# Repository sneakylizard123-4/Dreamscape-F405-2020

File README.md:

# Dreamscape F405

a 20x20mm flight controller for 3" fpv drone

## Why I made this

would be a nice portfolio project
if it works i save lots of money too

## Pictures

| Page | Sheet |
|---|---|
| 1 | [Root / block diagram](images/schematic/Dreamscape-F405-2020.png) |
| 2 | [Power](images/schematic/Dreamscape-F405-2020-Power.png) |
| 3 | [Sensors](images/schematic/Dreamscape-F405-2020-Sensors.png) |
| 4 | [Blackbox](images/schematic/Dreamscape-F405-2020-Blackbox.png) |
| 5 | [OSD](images/schematic/Dreamscape-F405-2020-OSD.png) |
| 6 | [STM32](images/schematic/Dreamscape-F405-2020-STM32.png) |
| 7 | [Pads / connectors](images/schematic/Dreamscape-F405-2020-Pads.png) |
| 8 | [USB](images/schematic/Dreamscape-F405-2020-USB.png) |

## Features

- **MCU**: STM32F405VGT6
- **IMU**: ICM-42688-P
- **Barometer**: BMP280
- **OSD**: AT7456E (MAX7456-compatible)
- **Blackbox**: full-size microSD slot
- **Receiver**: dedicated JST-SH 4-pin ExpressLRS connector
- **UARTs**: 4 exposed plus I2C pads
- **Power**:
  - Battery input up to 6S
  - 5 V rail: onboard buck regulator
  - 3.3 V rail: TLV75733 LDO
  - 10 V rail: separate buck to feed camera/VTX
  - Onboard battery voltage ADC divider and ESC current sensor input
- **Extras**: beeper driver, neopixel LED strip driver, status LEDs

## Power tree

```mermaid
graph LR
    BAT[Battery +BATT] --> BUCK10[LMR51430 buck]
    BAT --> BUCK5[LMR51430 buck]
    BUCK10 -->|10 V, switched by 10V_EN| R10[CAM / VTX]
    BUCK5 -->|+5V_BUCK| MUX[TPS2116 power mux]
    USB[USB +5V] --> MUX
    MUX -->|system +5V| PERIPH[OSD / ELRS / peripherals]
    PERIPH --> LDO[TLV75733 LDO]
    LDO -->|+3.3V| MCU[STM32F405 / sensors]
```

## Pinout

Solder pads along the edge:

| Pad | Function | Pad | Function |
|---|---|---|---|
| `BAT` | Battery positive | `G` | Ground |
| `3v3` | 3.3 V out | `5v` | 5 V out |
| `10v` | 10 V out (switchable) | `CUR` | ESC current sense in |
| `TEL` | ESC telemetry | `CC` | Camera control |
| `CAM` | Video in from camera | `VTX` | Video out to VTX |
| `M1`-`M4` | Motor PWM outputs | `LED` | Addressable LED strip |
| `BZ+`/`BZ-` | Beeper | `SDA`/`SCL` | I2C |
| `T1`/`R1` | UART1 TX/RX | `T2`/`R2` | UART2 TX/RX |
| `T3`/`R3` | UART3 TX/RX | `T6`/`R6` | UART6 TX/RX |

Connectors:

| Connector | Pins | Use |
|---|---|---|
| J41 - JST-SH 8-pin vertical | BAT, GND, CUR, TEL, M1-M4 | battery + ESC harness |
| J42 - JST-SH 4-pin horizontal | 5V, GND, TX, RX | ExpressLRS receiver |

## Assembly

you probably should get pcba

solder front side first.
hand solder back side

## Flashing

drag the `.bin` onto the mounted DFU drive using the Betaflight Configurator firmware flasher.

Notes:
- If DFU is not accessible, flash via SWD with an ST-Link and `STM32_Programmer_CLI` or OpenOCD instead.

## Known Issues

- Board hasn't been manufactured yet.

## Credits

- OpenDrone
- Betaflight project - firmware this board will run
- STMicroelectronics / TDK / Bosch / Analog Devices datasheets for part reference designs

---

## BOM

| Refs | Part | Package / Footprint | Notes |
|---|---|---|---|
| U1 | STM32F405VGT6 | LQFP-100 14x14 mm | main MCU, 168 MHz Cortex-M4 |
| U6 | ICM-42688-P | LGA-14 | gyro + accel |
| U7 | BMP280 | LGA-8 | barometer |
| U8 | AT7456E | TQFP | MAX7456-compatible OSD |
| Y1 | 27 MHz crystal | 2016 4-pad | OSD clock |
| Card1 | TF-021B-H265 | microSD push-pull slot | blackbox logging |
| U3, U4 | LMR51430 | SOT-23-6 | 3 A buck regulators (10 V and 5 V) |
| U5 | TPS2116DRLR | SOT-583-8 | USB/buck power mux |
| U2 | TLV75733PDBV | SOT-23-5 | 3.3 V LDO |
| Q5, Q6 | AP1606 | DFN-3 | beeper and LED strip drivers |
| D3, D6 | RB161QS-40 | SOD-882 | Schottky diodes (power path) |
| L2, L3 | XRTC303020D4R7 | 3x3 mm | 4.7 uH power inductors |
| D2 | Blue LED | 0402 | status |
| D4, D5, D7 | Green LED | 0402 | power indicators |
| J41 | JST-SH 8-pin | SM08B-SHLS-TF | battery/ESC harness |
| J42 | JST-SH 4-pin | SM04B-SRSS-TB | ELRS receiver |
| R31, R29, R27, R23, R50 | 100 kOhm x5 | 0201 | |
| R2, R39, R49, R50 | 10 kOhm x4 | 0201 | VBAT divider / pull-ups |
| R28 | 39 kOhm | 0201 | buck feedback divider |
| R34, R33 | 7.5 kOhm x2 | 0201 | buck feedback dividers |
| R32 | 13.7 kOhm | 0201 | buck feedback |
| R30 | 6.49 kOhm | 0201 | buck feedback |
| R53, R52 | 75 Ohm x2 | 0201 | |
| R36 | 510 Ohm | 0201 | |
| R51 | 2.4 kOhm | 0201 | |
| R9 | 1 kOhm | 0201 | current sensor filter |
| C24, C25 | 4.7 uF 50 V x2 | 0805 | battery input |
| C29, C28, C34 | 22 uF x3 | 0603/0402 | buck outputs |
| C30 | 4.7 uF | 0402 | |
| C1, C22 | 2.2 uF x2 | 0402 | |
| C4, C36-C39, C43, C32, C26, C27 | 100 nF x10 | 0201 | decoupling |

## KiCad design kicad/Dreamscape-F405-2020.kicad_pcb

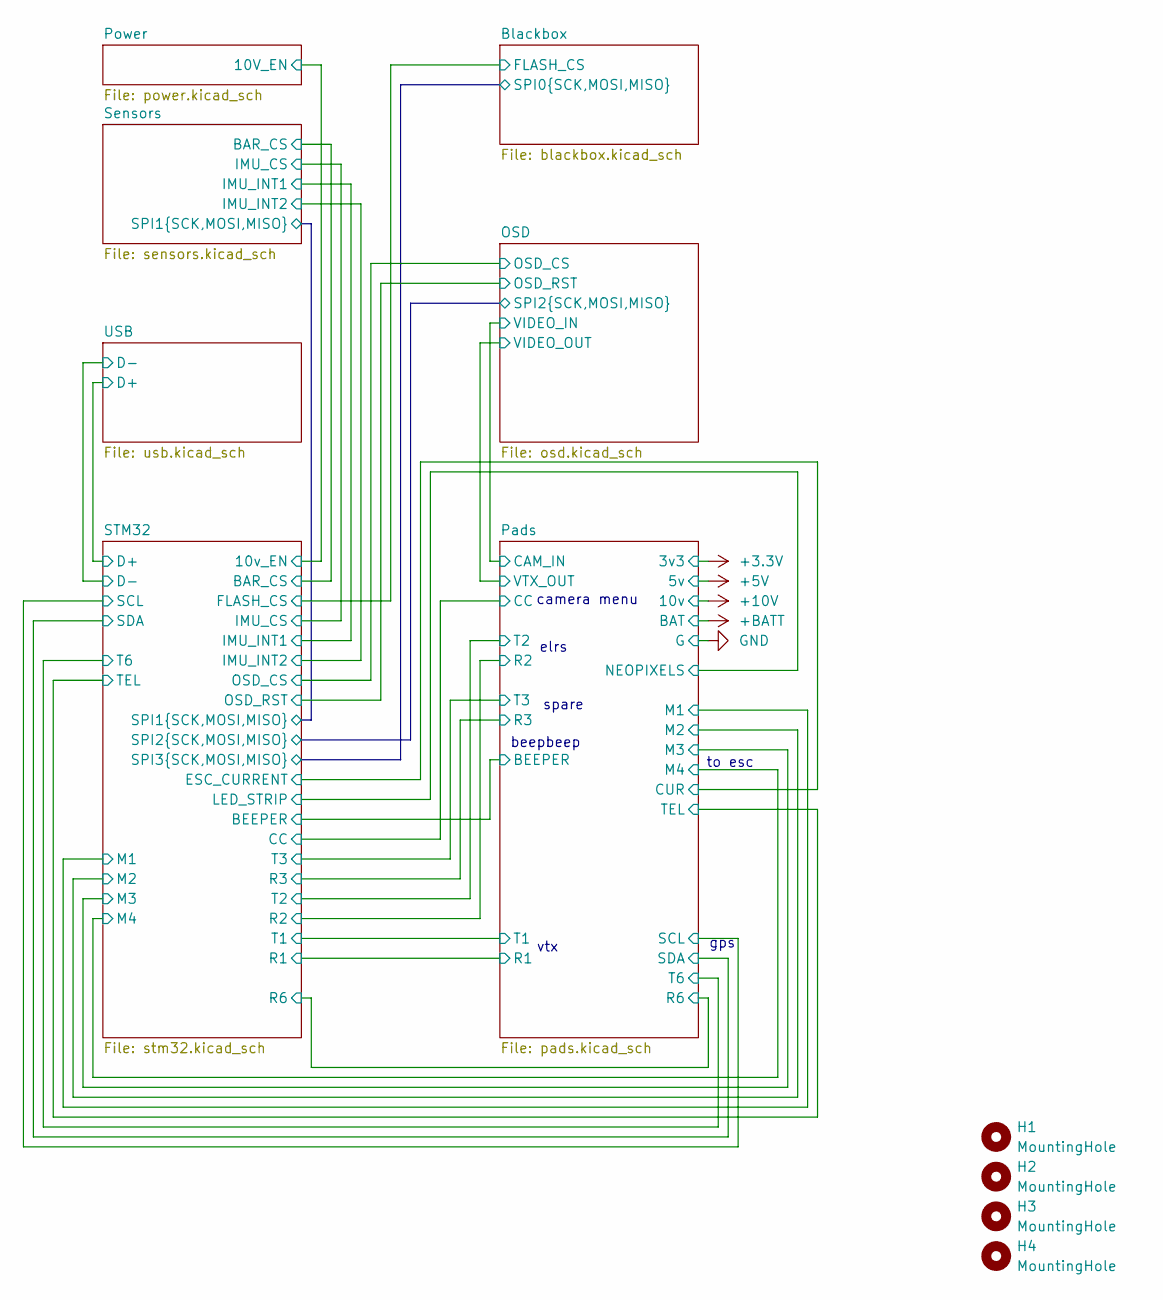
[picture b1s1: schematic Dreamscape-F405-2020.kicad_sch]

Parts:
H1, H2, H3, H4: MountingHole; MountingHole_3.2mm_M3

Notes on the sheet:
beepbeep
gps
spare
camera menu
elrs
to esc
vtx

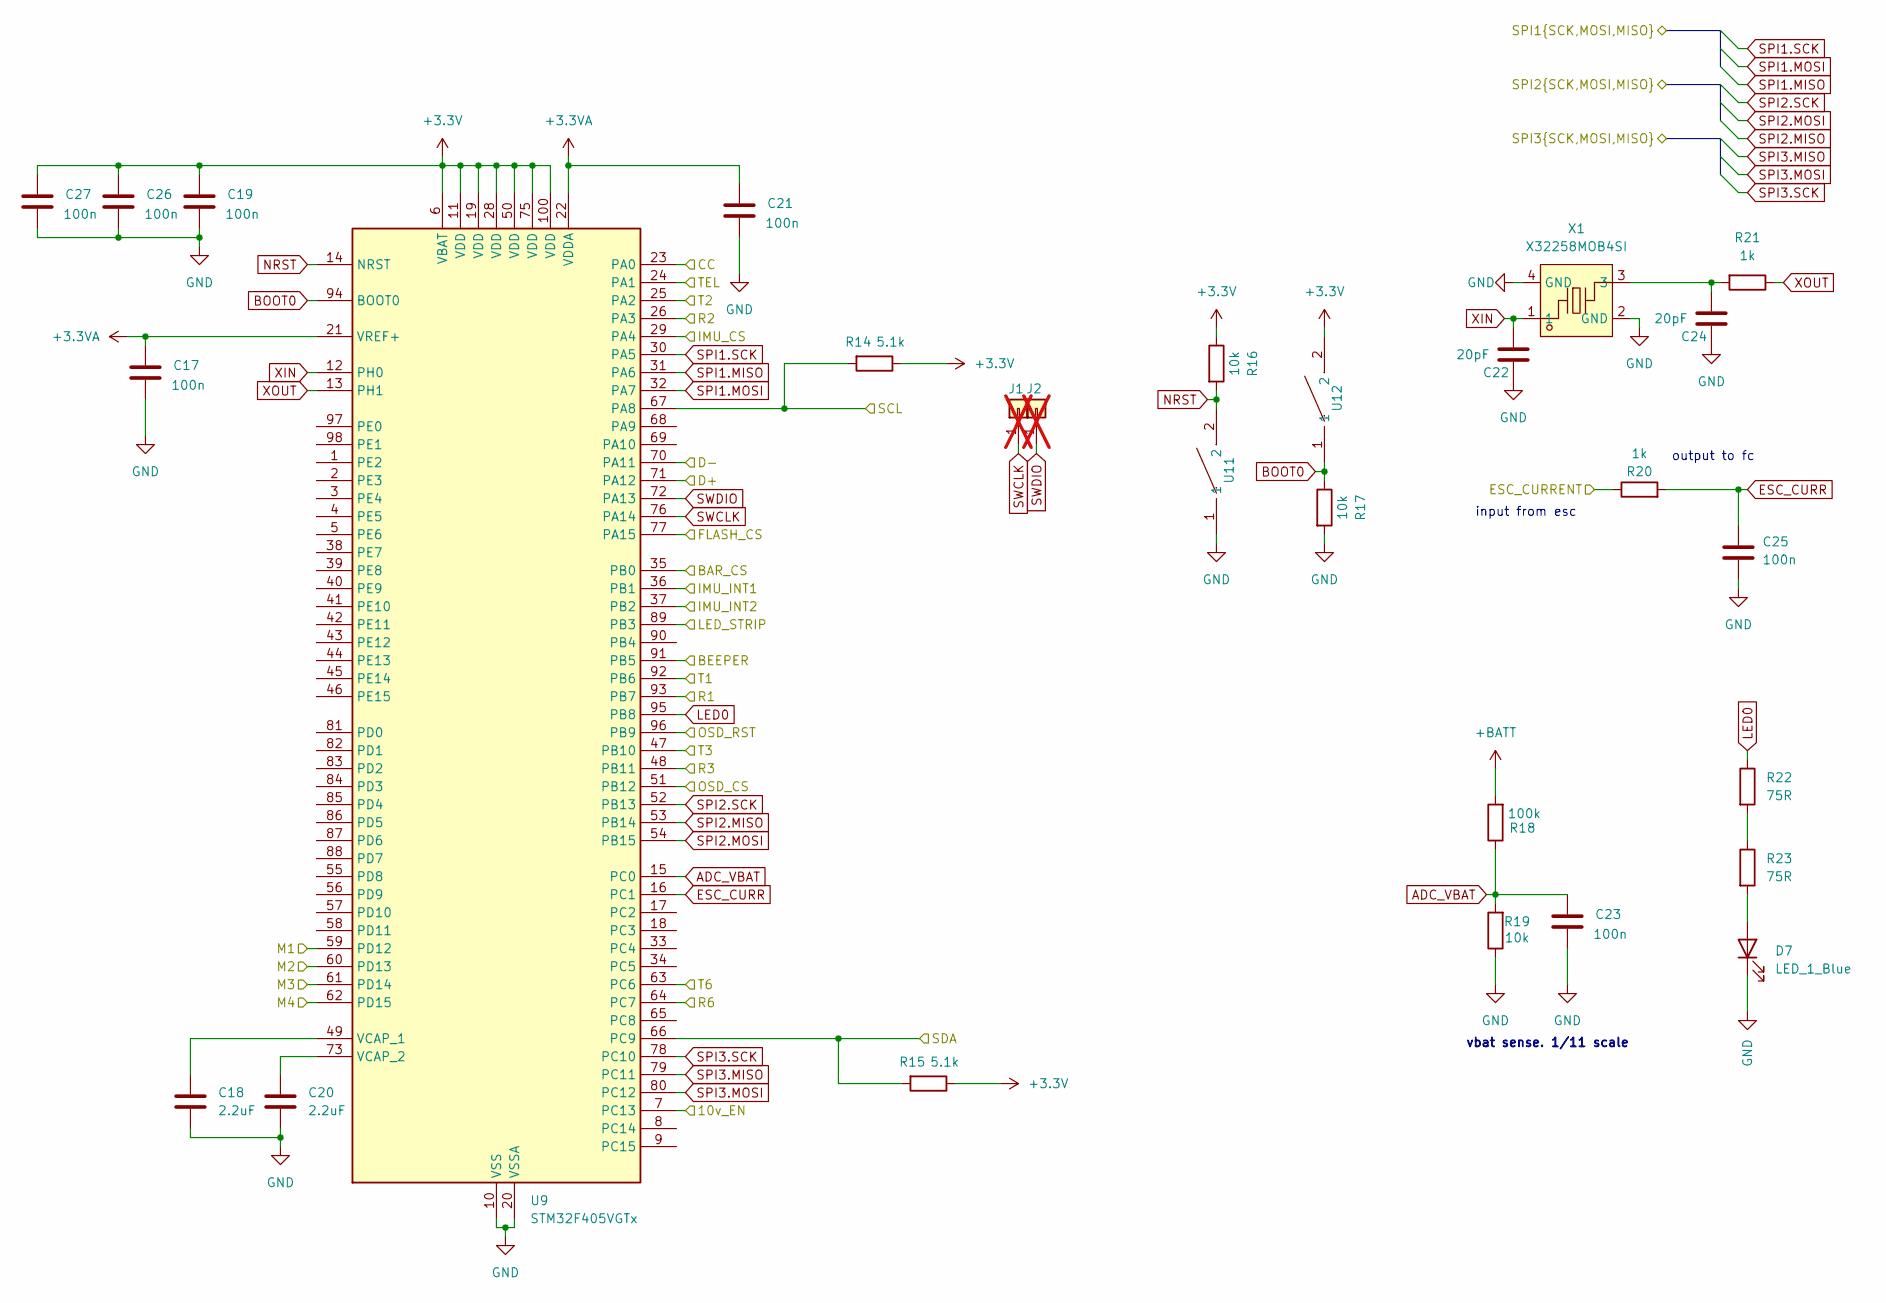
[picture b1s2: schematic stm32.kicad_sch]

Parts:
C17, C19, C21, C23, C25, C26, C27: 100n; C_0201_0603Metric; MPN GRM033R61E104KE14D; LCSC C76939
C18, C20: 2.2uF; C_0402_1005Metric
C22, C24: 20pF; C_0201_0603Metric; MPN GRM0335C1H200JA01D; LCSC C76923
D7: LED_1_Blue; LED_0402_1005Metric; MPN XL-1005UBC; LCSC C22355736
J1, J2: 5V; small_pad; not fitted
R14, R15: 5.1k; R_0201_0603Metric; MPN 0201WMF5101TEE; LCSC C270344
R16, R17, R19: 10k; R_0201_0603Metric; MPN RC0201FR-0710KL; LCSC C106225
R18: 100k; R_0201_0603Metric; MPN 0201WMF1003TEE; LCSC C270364
R20, R21: 1k; R_0201_0603Metric; MPN 0201WMF1001TEE; LCSC C270365
R22, R23: 75R; R_0201_0603Metric; MPN RC0201FR-0775RL; LCSC C274878
U9: STM32F405VGTx; LQFP-100_14x14mm_P0.5mm
U11, U12: TS2306A 240GF MSM 9_C2976675; SW-SMD_4P-L3.0-W2.0-P0.85-LS3.5; MPN TS2306A 240gf MSM 9; LCSC C2976675
X1: X32258MOB4SI; CRYSTAL-SMD_4P-L2.5-W2.0-BL-A; MPN X32258MOB4SI; LCSC C2682775

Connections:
+3.3V: C19.2, C26.2, C27.2, R14.1, R15.1, R16.1, U9.6 (VBAT), U9.11 (VDD), U9.19 (VDD), U9.28 (VDD), U9.50 (VDD), U9.75 (VDD), U9.100 (VDD), U12.2; also elsewhere on the board
+3.3VA: C17.2, C21.2, U9.21 (VREF+), U9.22 (VDDA); also elsewhere on the board
+BATT: R18.2; also elsewhere on the board
/Blackbox/FLASH_CS: U9.77 (PA15); also elsewhere on the board
/OSD/OSD_CS: U9.51 (PB12); also elsewhere on the board
/OSD/OSD_RST: U9.96 (PB9); also elsewhere on the board
/Pads/BEEPER: U9.91 (PB5); also elsewhere on the board
/Pads/CC: U9.23 (PA0); also elsewhere on the board
/Pads/CUR: R20.1; also elsewhere on the board
/Pads/M1: U9.59 (PD12); also elsewhere on the board
/Pads/M2: U9.60 (PD13); also elsewhere on the board
/Pads/M3: U9.61 (PD14); also elsewhere on the board
/Pads/M4: U9.62 (PD15); also elsewhere on the board
/Pads/NEOPIXELS: U9.89 (PB3); also elsewhere on the board
/Pads/R1: U9.93 (PB7); also elsewhere on the board
/Pads/R2: U9.26 (PA3); also elsewhere on the board
/Pads/R3: U9.48 (PB11); also elsewhere on the board
/Pads/R6: U9.64 (PC7); also elsewhere on the board
/Pads/SCL: R15.2, U9.66 (PC9); also elsewhere on the board
/Pads/SDA: R14.2, U9.67 (PA8); also elsewhere on the board
/Pads/T1: U9.92 (PB6); also elsewhere on the board
/Pads/T2: U9.25 (PA2); also elsewhere on the board
/Pads/T3: U9.47 (PB10); also elsewhere on the board
/Pads/T6: U9.63 (PC6); also elsewhere on the board
/Pads/TEL: U9.24 (PA1); also elsewhere on the board
/Power/10V_EN: U9.7 (PC13); also elsewhere on the board
/STM32/BAR_CS: U9.35 (PB0); also elsewhere on the board
/STM32/D+: U9.71 (PA12); also elsewhere on the board
/STM32/D-: U9.70 (PA11); also elsewhere on the board
/STM32/IMU_CS: U9.29 (PA4); also elsewhere on the board
/STM32/IMU_INT1: U9.36 (PB1); also elsewhere on the board
/STM32/IMU_INT2: U9.37 (PB2); also elsewhere on the board
ADC_VBAT: C23.2, R18.1, R19.2, U9.15 (PC0)
BOOT0: R17.1, U9.94 (BOOT0), U12.1
ESC_CURR: C25.1, R20.2, U9.16 (PC1)
GND: C17.1, C18.2, C19.1, C20.2, C21.1, C22.1, C23.1, C24.1, C25.2, C26.1, C27.1, D7.1 (K), R17.2, R19.1, U9.10 (VSS), U9.20 (VSSA), U9.27 (VSS), U9.74 (VSS), U9.99 (VSS), U11.1, X1.2 (GND), X1.4 (GND); also elsewhere on the board
LED0: R22.1, U9.95 (PB8)
NRST: R16.2, U9.14 (NRST), U11.2
unnamed: C24.2, R21.2, X1.3
unnamed: D7.2 (A), R23.2
unnamed: R22.2, R23.1
unnamed: C18.1, U9.49 (VCAP_1)
unnamed: C20.1, U9.73 (VCAP_2)
SPI1.MISO: U9.31 (PA6); also elsewhere on the board
SPI1.MOSI: U9.32 (PA7); also elsewhere on the board
SPI1.SCK: U9.30 (PA5); also elsewhere on the board
SPI2.MISO: U9.53 (PB14); also elsewhere on the board
SPI2.MOSI: U9.54 (PB15); also elsewhere on the board
SPI2.SCK: U9.52 (PB13); also elsewhere on the board
SPI3.MISO: U9.79 (PC11); also elsewhere on the board
SPI3.MOSI: U9.80 (PC12); also elsewhere on the board
SPI3.SCK: U9.78 (PC10); also elsewhere on the board
SWCLK: J1.1 (Pin_1_1), U9.76 (PA14)
SWDIO: J2.1 (Pin_1_1), U9.72 (PA13)
XIN: C22.2, U9.12 (PH0), X1.1
XOUT: R21.1, U9.13 (PH1)

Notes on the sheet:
input from esc
vbat sense. 1/11 scale
output to fc

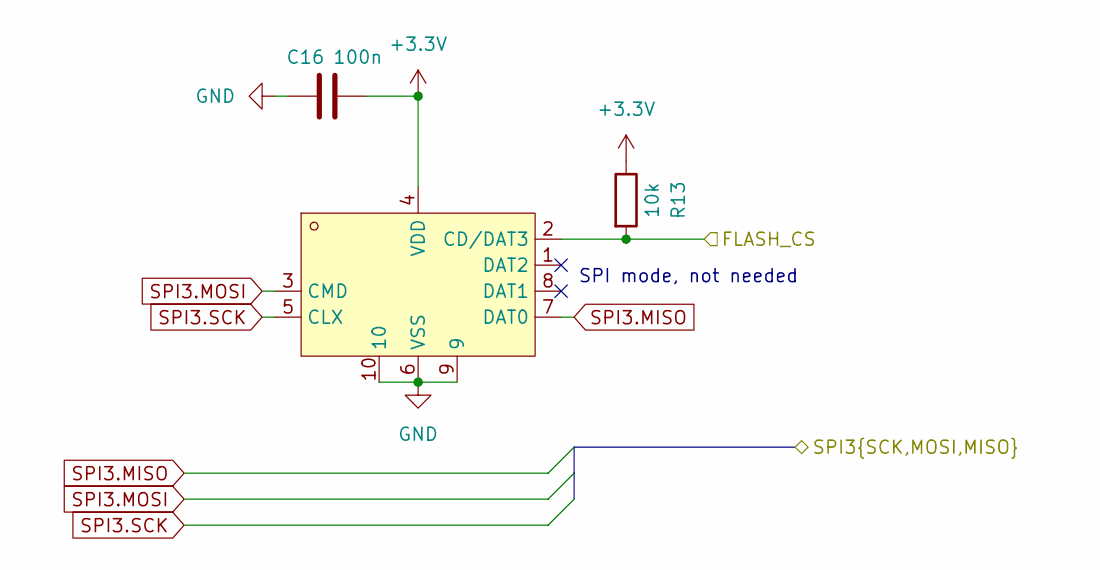
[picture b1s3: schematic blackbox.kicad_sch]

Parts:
C16: 100n; C_0201_0603Metric; MPN GRM033R61E104KE14D; LCSC C76939
Card1: TF-021B-H265; TF-SMD_TF-021B-H265; LCSC C498185
R13: 10k; R_0201_0603Metric; MPN RC0201FR-0710KL; LCSC C106225

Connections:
+3.3V: C16.1, Card1.4 (VDD), R13.1; also elsewhere on the board
/Blackbox/FLASH_CS: Card1.2 (CD/DAT3), R13.2; also elsewhere on the board
GND: C16.2, Card1.6 (VSS), Card1.9, Card1.10; also elsewhere on the board
SPI3.MISO: Card1.7 (DAT0); also elsewhere on the board
SPI3.MOSI: Card1.3 (CMD); also elsewhere on the board
SPI3.SCK: Card1.5 (CLX); also elsewhere on the board

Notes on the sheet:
SPI mode, not needed

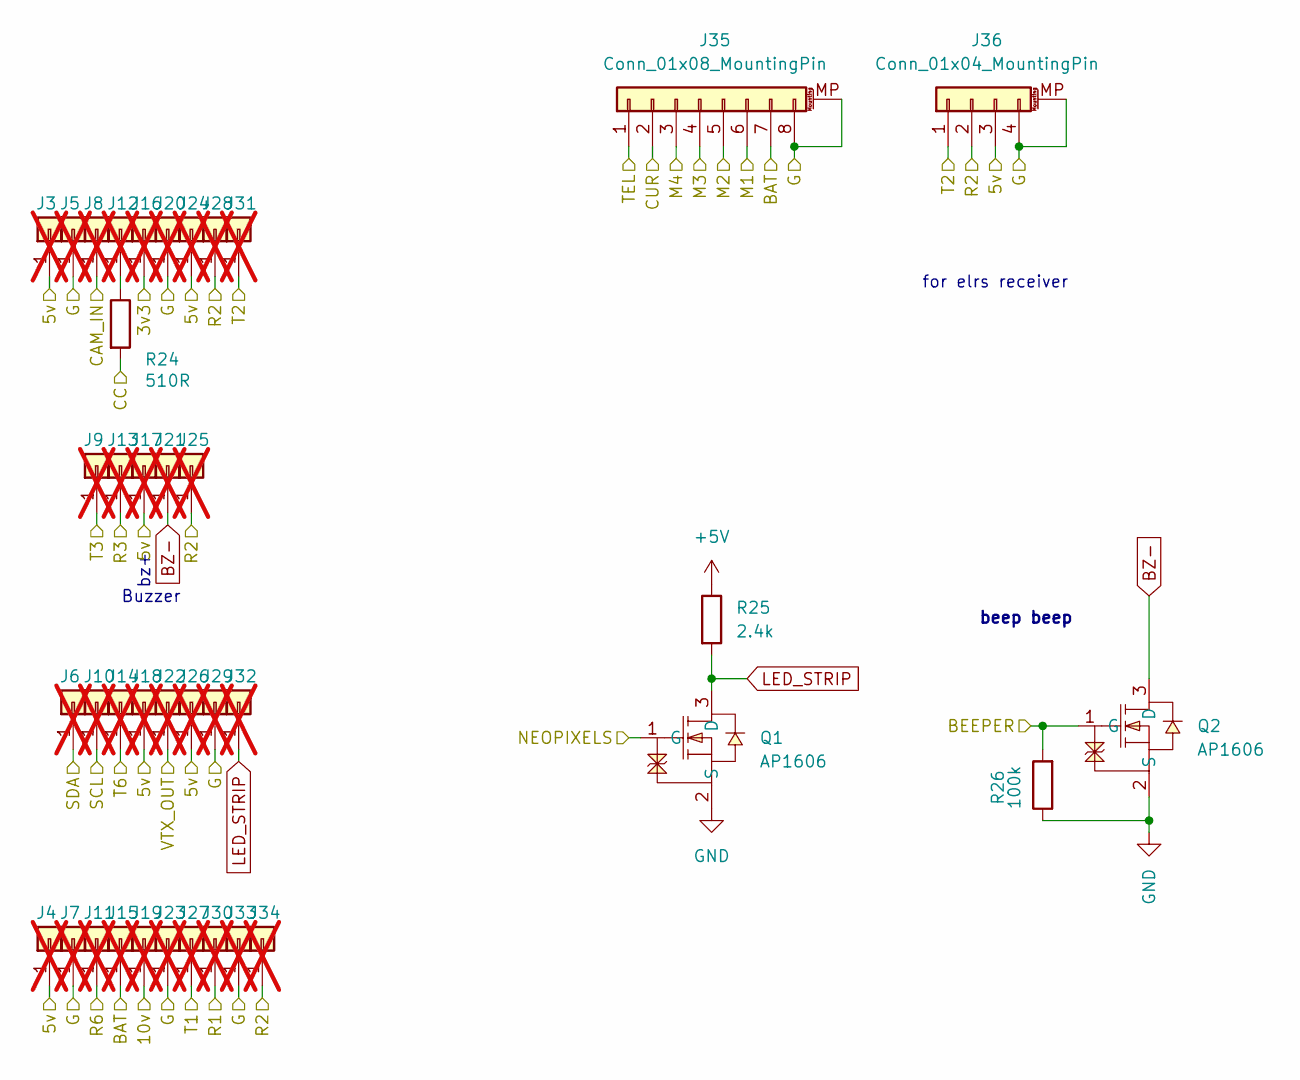
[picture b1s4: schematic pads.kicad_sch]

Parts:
J3, J4, J5, J6, J7, J8, J9, J10, J11, J12, J13, J14, J15, J16, J17, J18, J19, J20, J21, J22, J23, J24, J25, J26, J27, J28, J29, J30, J31, J32, J33, J34: 5V; small_pad; not fitted
J35: Conn_01x08_MountingPin; JST_SHL_SM08B-SHLS-TF_1x08-1MP_P1.00mm_Horizontal
J36: Conn_01x04_MountingPin; JST_SH_SM04B-SRSS-TB_1x04-1MP_P1.00mm_Horizontal
Q1, Q2: AP1606; DFN-3L_L1.0-W0.6-P0.65-BR; MPN AP1606; LCSC C2849580
R24: 510R; R_0201_0603Metric; LCSC C57784
R25: 2.4k; R_0201_0603Metric; LCSC C166281
R26: 100k; R_0201_0603Metric; MPN 0201WMF1003TEE; LCSC C270364

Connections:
+3.3V: J16.1 (Pin_1_1); also elsewhere on the board
+5V: J3.1 (Pin_1_1), J4.1 (Pin_1_1), J17.1 (Pin_1_1), J18.1 (Pin_1_1), J24.1 (Pin_1_1), J26.1 (Pin_1_1), J36.3, R25.1; also elsewhere on the board
+10V: J19.1 (Pin_1_1); also elsewhere on the board
+BATT: J15.1 (Pin_1_1), J35.7; also elsewhere on the board
/OSD/VIDEO_IN: J8.1 (Pin_1_1); also elsewhere on the board
/OSD/VIDEO_OUT: J22.1 (Pin_1_1); also elsewhere on the board
/Pads/BEEPER: Q2.1 (G), R26.2; also elsewhere on the board
/Pads/CC: R24.2; also elsewhere on the board
/Pads/CUR: J35.2; also elsewhere on the board
/Pads/M1: J35.6; also elsewhere on the board
/Pads/M2: J35.5; also elsewhere on the board
/Pads/M3: J35.4; also elsewhere on the board
/Pads/M4: J35.3; also elsewhere on the board
/Pads/NEOPIXELS: Q1.1 (G); also elsewhere on the board
/Pads/R1: J30.1 (Pin_1_1); also elsewhere on the board
/Pads/R2: J25.1 (Pin_1_1), J28.1 (Pin_1_1), J34.1 (Pin_1_1), J36.2; also elsewhere on the board
/Pads/R3: J13.1 (Pin_1_1); also elsewhere on the board
/Pads/R6: J11.1 (Pin_1_1); also elsewhere on the board
/Pads/SCL: J10.1 (Pin_1_1); also elsewhere on the board
/Pads/SDA: J6.1 (Pin_1_1); also elsewhere on the board
/Pads/T1: J27.1 (Pin_1_1); also elsewhere on the board
/Pads/T2: J31.1 (Pin_1_1), J36.1; also elsewhere on the board
/Pads/T3: J9.1 (Pin_1_1); also elsewhere on the board
/Pads/T6: J14.1 (Pin_1_1); also elsewhere on the board
/Pads/TEL: J35.1; also elsewhere on the board
BZ-: J21.1 (Pin_1_1), Q2.3 (D)
GND: J5.1 (Pin_1_1), J7.1 (Pin_1_1), J20.1 (Pin_1_1), J23.1 (Pin_1_1), J29.1 (Pin_1_1), J33.1 (Pin_1_1), J35.8, J35.MP (MountPin), J36.4, J36.MP (MountPin), Q1.2 (S), Q2.2 (S), R26.1; also elsewhere on the board
LED_STRIP: J32.1 (Pin_1_1), Q1.3 (D), R25.2
unnamed: J12.1 (Pin_1_1), R24.1

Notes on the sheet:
Buzzer
beep beep
bz+
for elrs receiver

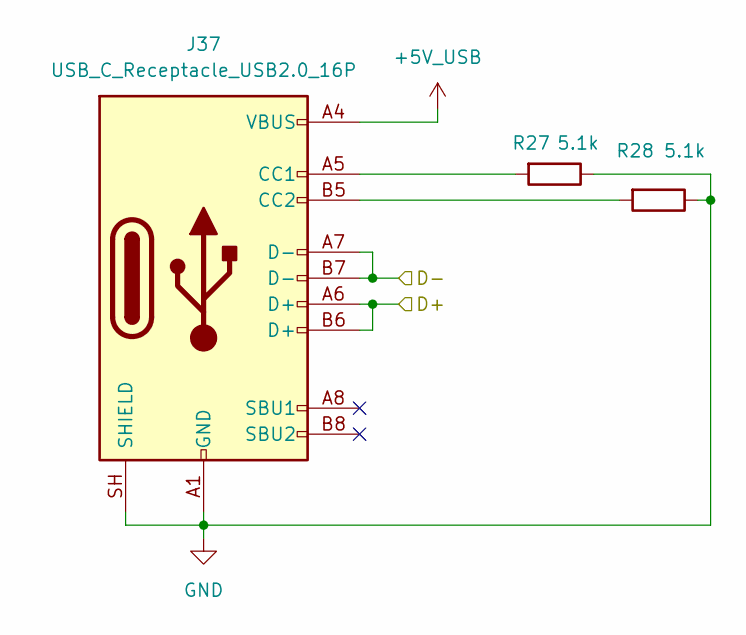
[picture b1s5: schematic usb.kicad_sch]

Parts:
J37: USB_C_Receptacle_USB2.0_16P; USB_C_Receptacle_HRO_TYPE-C-31-M-12
R27, R28: 5.1k; R_0201_0603Metric; MPN 0201WMF5101TEE; LCSC C270344

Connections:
+5V_USB: J37.A4 (VBUS), J37.A9 (VBUS), J37.B4 (VBUS), J37.B9 (VBUS); also elsewhere on the board
/STM32/D+: J37.A6 (D+), J37.B6 (D+); also elsewhere on the board
/STM32/D-: J37.A7 (D-), J37.B7 (D-); also elsewhere on the board
GND: J37.A1 (GND), J37.A12 (GND), J37.B1 (GND), J37.B12 (GND), J37.SH (SHIELD), R27.1, R28.1; also elsewhere on the board
unnamed: J37.A5 (CC1), R27.2
unnamed: J37.B5 (CC2), R28.2

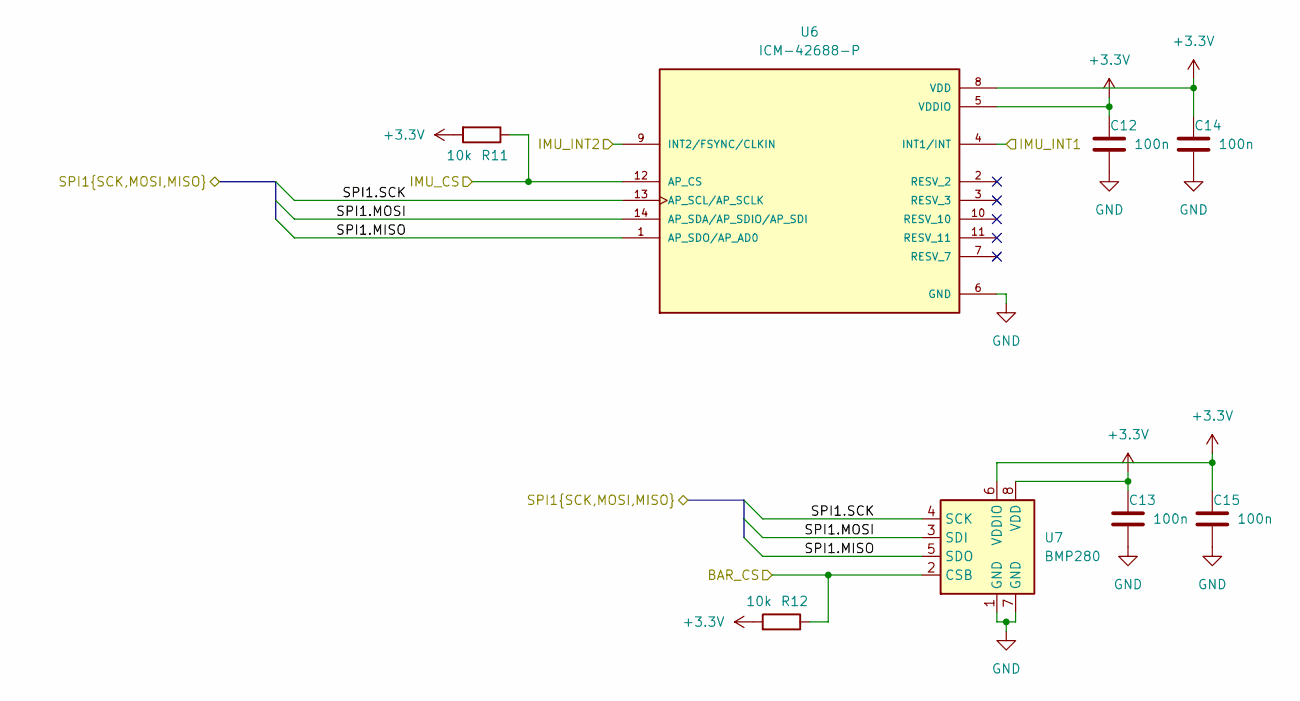
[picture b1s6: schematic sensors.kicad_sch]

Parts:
C12, C13, C14, C15: 100n; C_0201_0603Metric; MPN GRM033R61E104KE14D; LCSC C76939
R11, R12: 10k; R_0201_0603Metric; MPN RC0201FR-0710KL; LCSC C106225
U6: ICM-42688-P; PQFN50P300X250X97-14N; PARTREV 1.2
U7: BMP280; Bosch_LGA-8_2x2.5mm_P0.65mm_ClockwisePinNumbering

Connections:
+3.3V: C12.1, C13.1, C14.1, C15.1, R11.2, R12.2, U6.5 (VDDIO), U6.8 (VDD), U7.6 (VDDIO), U7.8 (VDD); also elsewhere on the board
/STM32/BAR_CS: R12.1, U7.2 (CSB); also elsewhere on the board
/STM32/IMU_CS: R11.1, U6.12 (AP_CS); also elsewhere on the board
/STM32/IMU_INT1: U6.4 (INT1/INT); also elsewhere on the board
/STM32/IMU_INT2: U6.9 (INT2/FSYNC/CLKIN); also elsewhere on the board
GND: C12.2, C13.2, C14.2, C15.2, U6.6 (GND), U7.1 (GND), U7.7 (GND); also elsewhere on the board
SPI1.MISO: U6.1 (AP_SDO/AP_AD0), U7.5 (SDO); also elsewhere on the board
SPI1.MOSI: U6.14 (AP_SDA/AP_SDIO/AP_SDI), U7.3 (SDI); also elsewhere on the board
SPI1.SCK: U6.13 (AP_SCL/AP_SCLK), U7.4 (SCK); also elsewhere on the board

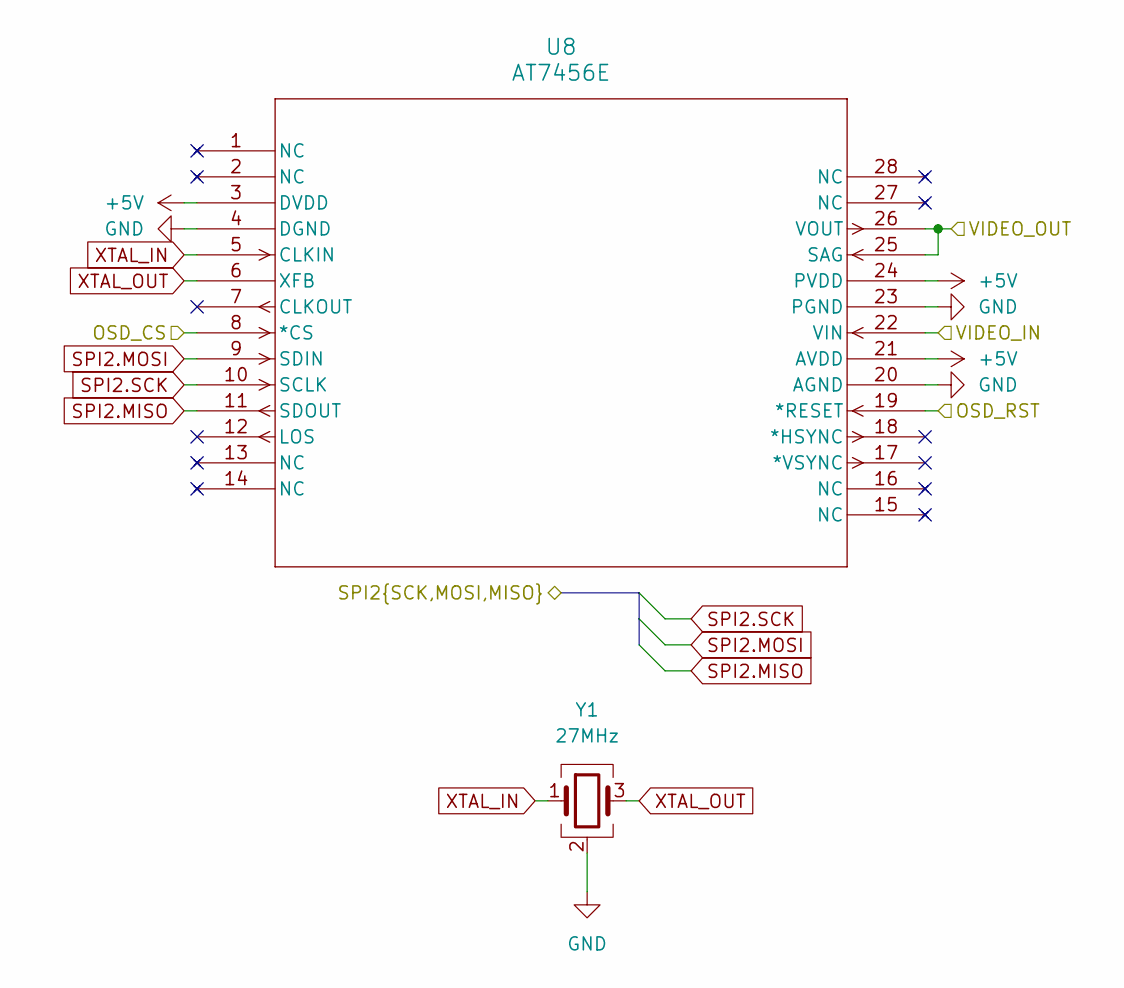
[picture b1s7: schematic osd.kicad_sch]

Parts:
U8: AT7456E; 21-0108G_U28E-5_MXM
Y1: 27MHz; Crystal_SMD_2016-4Pin_2.0x1.6mm

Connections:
+5V: U8.3 (DVDD), U8.21 (AVDD), U8.24 (PVDD); also elsewhere on the board
/OSD/OSD_CS: U8.8 (*CS); also elsewhere on the board
/OSD/OSD_RST: U8.19 (*RESET); also elsewhere on the board
/OSD/VIDEO_IN: U8.22 (VIN); also elsewhere on the board
/OSD/VIDEO_OUT: U8.25 (SAG), U8.26 (VOUT); also elsewhere on the board
GND: U8.4 (DGND), U8.20 (AGND), U8.23 (PGND), Y1.2 (G), Y1.4 (G); also elsewhere on the board
SPI2.MISO: U8.11 (SDOUT); also elsewhere on the board
SPI2.MOSI: U8.9 (SDIN); also elsewhere on the board
SPI2.SCK: U8.10 (SCLK); also elsewhere on the board
XTAL_IN: U8.5 (CLKIN), Y1.1
XTAL_OUT: U8.6 (XFB), Y1.3

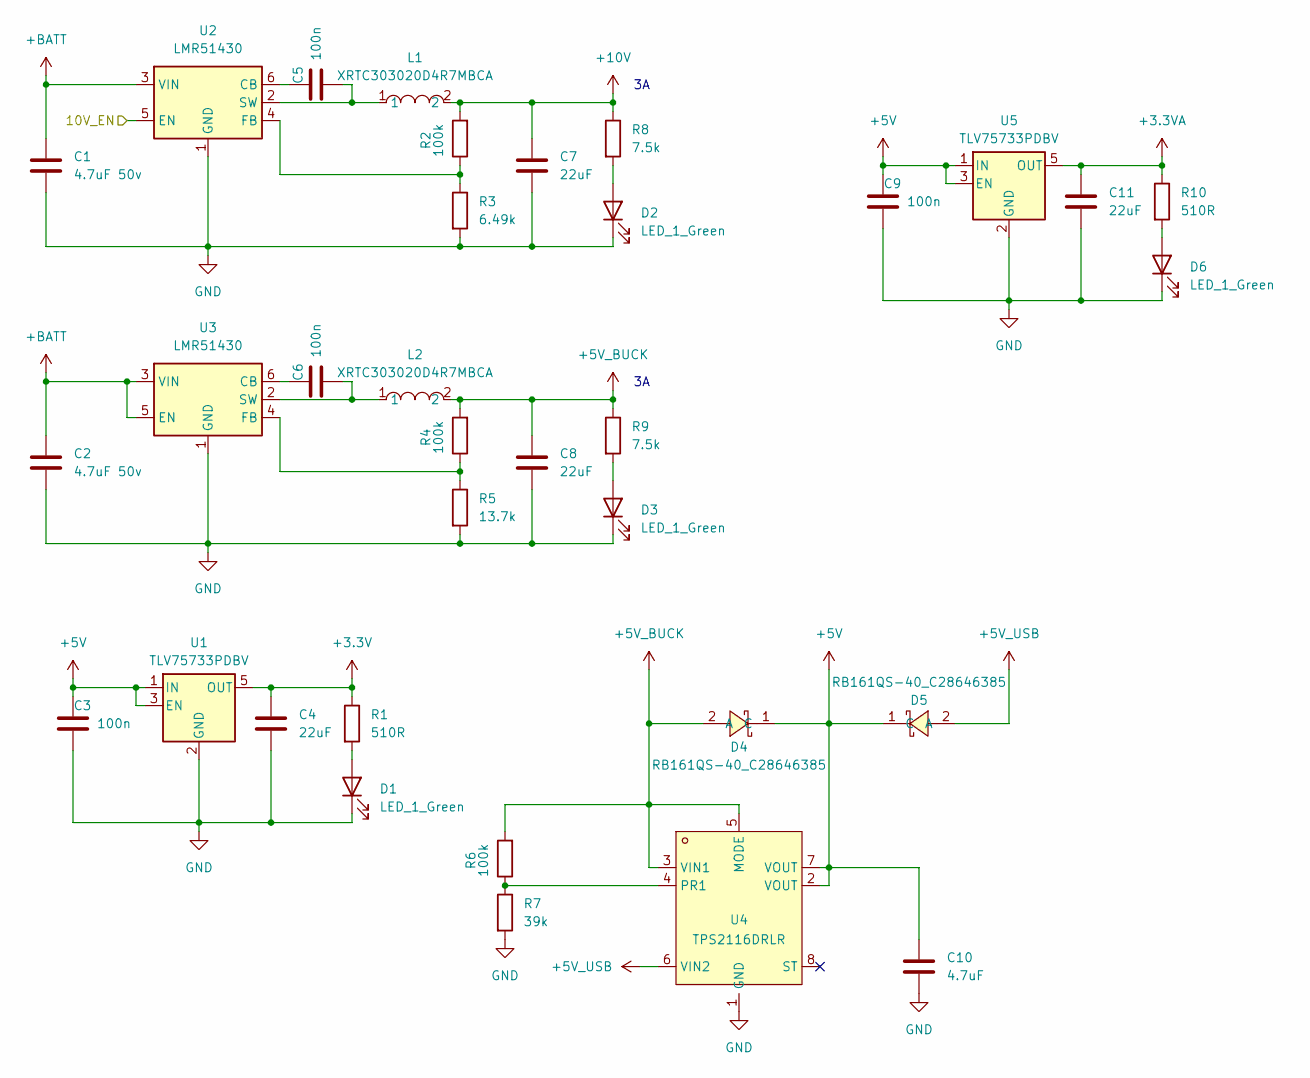
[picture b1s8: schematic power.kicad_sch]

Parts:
C1, C2: 4.7uF 50v; C_0805_2012Metric; MPN CL21A475KBQNNNE; LCSC C98192
C3, C5, C6, C9: 100n; C_0201_0603Metric; MPN GRM033R61E104KE14D; LCSC C76939
C4, C11: 22uF; C_0402_1005Metric; MPN GRM155R60J226ME11D; LCSC C415703
C7, C8: 22uF; C_0603_1608Metric; MPN CL10A226MO7JZNC; LCSC C2762594
C10: 4.7uF; C_0402_1005Metric; MPN CL05A475MP5NRNC; LCSC C23733
D1, D2, D3, D6: LED_1_Green; LED_0402_1005Metric; MPN XL-1005UGC; LCSC C965793
D4, D5: RB161QS-40_C28646385; D_SOD-882; MPN RB161QS-40; LCSC C28646385
L1, L2: XRTC303020D4R7MBCA; IND-SMD_L3.0-W3.0_AFE303020S; MPN XRTC303020D4R7MBCA; LCSC C39846837
R1, R10: 510R; R_0201_0603Metric; LCSC C57784
R2, R4, R6: 100k; R_0201_0603Metric; MPN 0201WMF1003TEE; LCSC C270364
R3: 6.49k; R_0201_0603Metric; LCSC C2107920
R5: 13.7k; R_0201_0603Metric; MPN RC-01W1372FT; LCSC C320695
R7: 39k; R_0201_0603Metric; MPN 0201WMF3902TEE; LCSC C473053
R8, R9: 7.5k; R_0201_0603Metric; LCSC C474437
U1, U5: TLV75733PDBV; SOT-23-5
U2, U3: LMR51430; SOT-23-6
U4: TPS2116DRLR; SOT-583-8_L2.1-W1.6-P0.50-LS1.6-BL; MPN TPS2116DRLR; LCSC C3235557

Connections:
+3.3V: C4.1, R1.1, U1.5 (OUT); also elsewhere on the board
+3.3VA: C11.1, R10.1, U5.5 (OUT); also elsewhere on the board
+5V: C3.1, C9.1, C10.1, D4.1 (C), D5.1 (C), U1.1 (IN), U1.3 (EN), U4.2 (VOUT), U4.7 (VOUT), U5.1 (IN), U5.3 (EN); also elsewhere on the board
+5V_BUCK: C8.1, D4.2 (A), L2.2, R4.2, R6.2, R9.1, U4.3 (VIN1), U4.5 (MODE)
+5V_USB: D5.2 (A), U4.6 (VIN2); also elsewhere on the board
+10V: C7.1, L1.2, R2.2, R8.1; also elsewhere on the board
+BATT: C1.1, C2.1, U2.3 (VIN), U3.3 (VIN), U3.5 (EN); also elsewhere on the board
/Power/10V_EN: U2.5 (EN); also elsewhere on the board
GND: C1.2, C2.2, C3.2, C4.2, C7.2, C8.2, C9.2, C10.2, C11.2, D1.1 (K), D2.1 (K), D3.1 (K), D6.1 (K), R3.2, R5.2, R7.2, U1.2 (GND), U2.1 (GND), U3.1 (GND), U4.1 (GND), U5.2 (GND); also elsewhere on the board
unnamed: D1.2 (A), R1.2
unnamed: D2.2 (A), R8.2
unnamed: D3.2 (A), R9.2
unnamed: D6.2 (A), R10.2
unnamed: C5.1, U2.6 (CB)
unnamed: R2.1, R3.1, U2.4 (FB)
unnamed: C5.2, L1.1, U2.2 (SW)
unnamed: C6.1, U3.6 (CB)
unnamed: R4.1, R5.1, U3.4 (FB)
unnamed: C6.2, L2.1, U3.2 (SW)
unnamed: R6.1, R7.1, U4.4 (PR1)

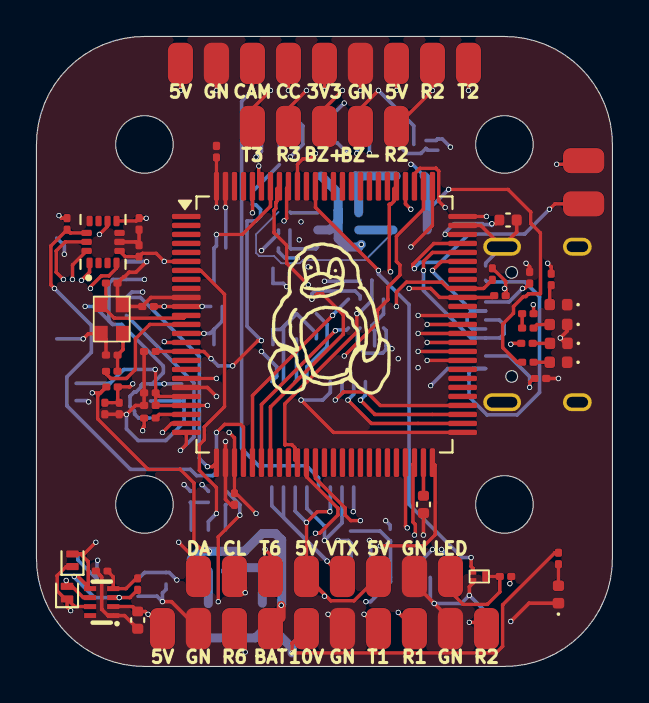
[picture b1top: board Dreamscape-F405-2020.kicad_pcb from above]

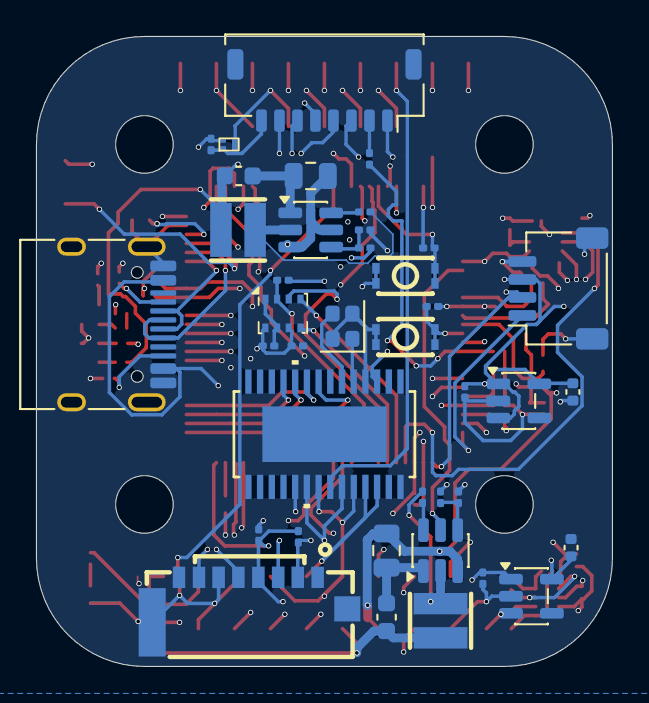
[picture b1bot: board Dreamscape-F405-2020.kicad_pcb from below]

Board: 6 copper layers, 32.0 x 35.0 mm, 121 parts (39 on the bottom side), 80 nets.

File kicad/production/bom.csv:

Designator,Footprint,Quantity,Value,LCSC Part #
"C1, C2",0805,2,4.7uF 50v,C98192
C10,0402,1,4.7uF,C23733
"C11, C4",0402,2,22uF,C415703
"C12, C13, C14, C15, C16, C17, C19, C21, C23, C25, C26, C27, C3, C5, C6, C9",0201,16,100n,C76939
"C18, C20",0402,2,2.2uF,
"C22, C24",0201,2,20pF,C76923
"C7, C8",0603,2,22uF,C2762594
CARD1,TF-SMD_TF-021B-H265,1,TF-021B-H265,C498185
"D1, D2, D3, D6",0402,4,LED_1_Green,C965793
"D4, D5",D_SOD-882,2,RB161QS-40_C28646385,C28646385
D7,0402,1,LED_1_Blue,C22355736
J35,JST_SHL_SM08B-SHLS-TF_1x08-1MP_P1.00mm_Horizontal,1,Conn_01x08_MountingPin,
J36,JST_SH_SM04B-SRSS-TB_1x04-1MP_P1.00mm_Horizontal,1,Conn_01x04_MountingPin,
J37,USB_C_Receptacle_HRO_TYPE-C-31-M-12,1,USB_C_Receptacle_USB2.0_16P,
"L1, L2",IND-SMD_L3.0-W3.0_AFE303020S,2,XRTC303020D4R7MBCA,C39846837
"Q1, Q2",DFN-3L_L1.0-W0.6-P0.65-BR,2,AP1606,C2849580
"R1, R10, R24",0201,3,510R,C57784
"R11, R12, R13, R16, R17, R19",0201,6,10k,C106225
"R14, R15, R27, R28",0201,4,5.1k,C270344
"R18, R2, R26, R4, R6",0201,5,100k,C270364
"R20, R21",0201,2,1k,C270365
"R22, R23",0201,2,75R,C274878
R25,0201,1,2.4k,C166281
R3,0201,1,6.49k,C2107920
R5,0201,1,13.7k,C320695
R7,0201,1,39k,C473053
"R8, R9",0201,2,7.5k,C474437
"U1, U5",SOT-23-5,2,TLV75733PDBV,
"U11, U12",SW-SMD_4P-L3.0-W2.0-P0.85-LS3.5,2,TS2306A 240GF MSM 9_C2976675,C2976675
"U2, U3",SOT-23-6,2,LMR51430,
U4,SOT-583-8_L2.1-W1.6-P0.50-LS1.6-BL,1,TPS2116DRLR,C3235557
U6,PQFN50P300X250X97-14N,1,ICM-42688-P,
U7,Bosch_LGA-8_2x2.5mm_P0.65mm_ClockwisePinNumbering,1,BMP280,
U8,21-0108G_U28E-5_MXM,1,AT7456E,
U9,LQFP-100_14x14mm_P0.5mm,1,STM32F405VGTx,
X1,CRYSTAL-SMD_4P-L2.5-W2.0-BL-A,1,X32258MOB4SI,C2682775
Y1,Crystal_SMD_2016-4Pin_2.0x1.6mm,1,27MHz,
